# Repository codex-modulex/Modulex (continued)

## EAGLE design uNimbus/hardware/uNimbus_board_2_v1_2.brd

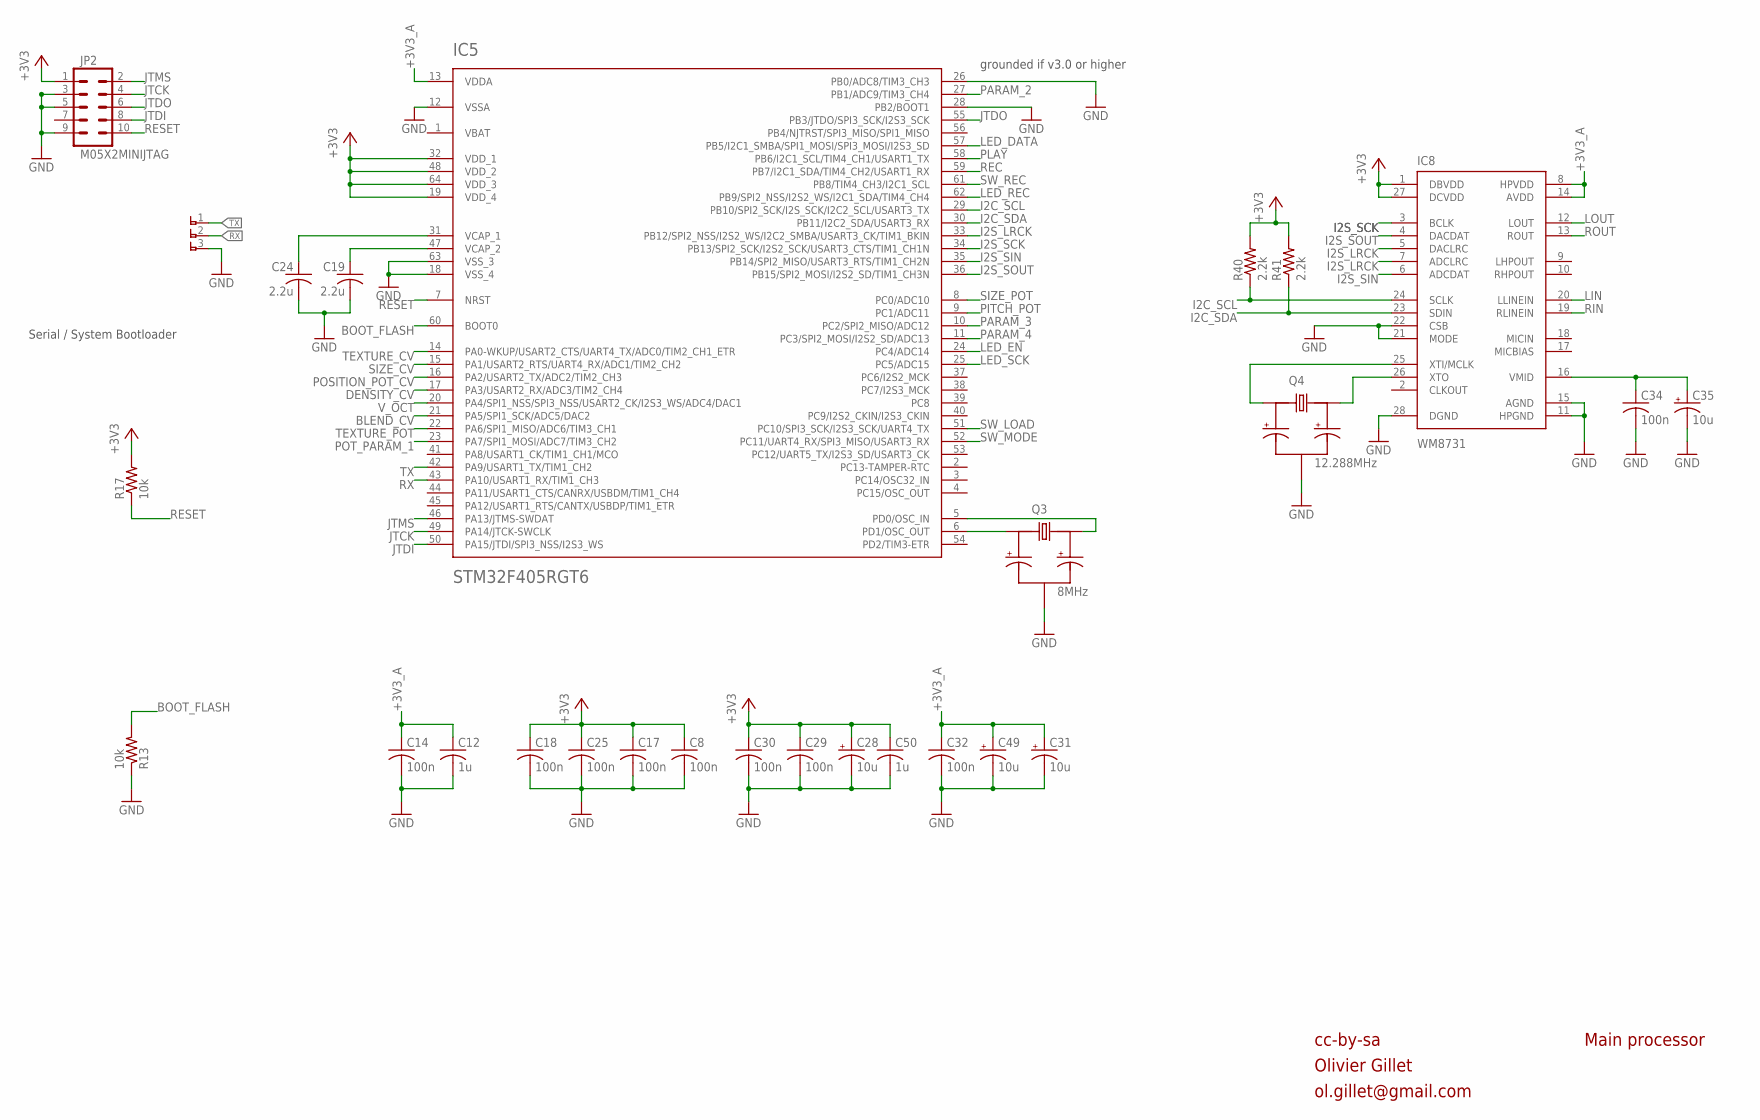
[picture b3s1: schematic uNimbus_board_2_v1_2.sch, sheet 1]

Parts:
C8, C32, C34: 100n; C0603
C12, C50: 1u; C0603K
C14, C17, C18, C25, C29, C30: 100n; C0603K
C19, C24: 2.2u; C0805K
C28: 10u; 153CLV-0405
C31, C35: 10u; PANASONIC_B
C49: 10u; PANASONIC_A
IC5: STM32F405RGT6; TQFP-10X10-64
IC8: WM8731; SSOP28
JP2: M05X2MINIJTAG; 2X5-1.27
Q3: 8MHz; CRYSTAL_SMALLER
Q4: 12.288MHz; CRYSTAL_SMALLER
R13, R17: 10k; PARTS_AMAN_RESISTOR_0603
R40, R41: 2.2k; PARTS_AMAN_RESISTOR_0603
U$4: 1X3_SMALL

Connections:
+3V3: C8.1, C17.1, C18.1, C25.1, C28.+, C29.1, C30.1, C50.1, IC5.19 (VDD_4), IC5.32 (VDD_1), IC5.48 (VDD_2), IC5.64 (VDD_3), IC8.1 (DBVDD), IC8.27 (DCVDD), JP2.1, R17.2, R40.2, R41.2; also elsewhere on the board
+3V3_A: C12.1, C14.1, C31.+, C32.1, C49.+, IC5.13 (VDDA), IC8.8 (HPVDD), IC8.14 (AVDD); also elsewhere on the board
BLEND_CV: IC5.21 (PA5/SPI1_SCK/ADC5/DAC2); also elsewhere on the board
BOOT_FLASH: IC5.60 (BOOT0), R13.2
DENSITY_CV: IC5.17 (PA3/USART2_RX/ADC3/TIM2_CH4); also elsewhere on the board
GND: C8.2, C12.2, C14.2, C17.2, C18.2, C19.2, C24.2, C25.2, C28.-, C29.2, C30.2, C31.-, C32.2, C34.2, C35.-, C49.-, C50.2, IC5.12 (VSSA), IC5.18 (VSS_4), IC5.26 (PB0/ADC8/TIM3_CH3), IC5.28 (PB2/BOOT1), IC5.63 (VSS_3), IC8.11 (HPGND), IC8.15 (AGND), IC8.21 (MODE), IC8.22 (CSB), IC8.28 (DGND), JP2.3, JP2.5, JP2.9, Q3.GND, Q4.GND, R13.1, U$4.3; also elsewhere on the board
I2C_SCL: IC5.29 (PB10/SPI2_SCK/I2S_SCK/I2C2_SCL/USART3_TX), IC8.24 (SCLK), R40.1
I2C_SDA: IC5.30 (PB11/I2C2_SDA/USART3_RX), IC8.23 (SDIN), R41.1
I2S_LRCK: IC5.33 (PB12/SPI2_NSS/I2S2_WS/I2C2_SMBA/USART3_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), IC8.5 (DACLRC), IC8.7 (ADCLRC)
I2S_SCK: IC5.34 (PB13/SPI2_SCK/I2S2_SCK/USART3_CTS/TIM1_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), IC8.3 (BCLK)
I2S_SIN: IC5.35 (PB14/SPI2_MISO/USART3_RTS/TIM1_CH2N), IC8.6 (ADCDAT)
I2S_SOUT: IC5.36 (PB15/SPI2_MOSI/I2S2_SD/TIM1_CH3N), IC8.4 (DACDAT)
JTCK: IC5.49 (PA14/JTCK-SWCLK), JP2.4
JTDI: IC5.50 (PA15/JTDI/SPI3_NSS/I2S3_WS), JP2.8
JTDO: IC5.55 (PB3/JTDO/SPI3_SCK/I2S3_SCK), JP2.6
JTMS: IC5.46 (PA13/JTMS-SWDAT), JP2.2
LED_DATA: IC5.57 (PB5/I2C1_SMBA/SPI1_MOSI/SPI3_MOSI/I2S3_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); also elsewhere on the board
LED_EN: IC5.24 (PC4/ADC14); also elsewhere on the board
LED_REC: IC5.62 (PB9/SPI2_NSS/I2S2_WS/I2C1_SDA/TIM4_CH4); also elsewhere on the board
LED_SCK: IC5.25 (PC5/ADC15); also elsewhere on the board
LIN: IC8.20 (LLINEIN); also elsewhere on the board
LOUT: IC8.12 (LOUT); also elsewhere on the board
unnamed: IC5.6 (PD1/OSC_OUT), Q3.X1
unnamed: IC8.25 (XTI/MCLK), Q4.X1
unnamed: IC5.5 (PD0/OSC_IN), Q3.X2
unnamed: C19.1, IC5.47 (VCAP_2)
unnamed: C34.1, C35.+, IC8.16 (VMID)
unnamed: C24.1, IC5.31 (VCAP_1)
unnamed: IC8.26 (XTO), Q4.X2
PARAM_2: IC5.27 (PB1/ADC9/TIM3_CH4); also elsewhere on the board
PARAM_3: IC5.10 (PC2/SPI2_MISO/ADC12); also elsewhere on the board
PARAM_4: IC5.11 (PC3/SPI2_MOSI/I2S2_SD/ADC13); also elsewhere on the board
PITCH_POT: IC5.9 (PC1/ADC11); also elsewhere on the board
PLAY: IC5.58 (PB6/I2C1_SCL/TIM4_CH1/USART1_TX); also elsewhere on the board
POSITION_POT_CV: IC5.16 (PA2/USART2_TX/ADC2/TIM2_CH3); also elsewhere on the board
POT_PARAM_1: IC5.23 (PA7/SPI1_MOSI/ADC7/TIM3_CH2); also elsewhere on the board
REC: IC5.59 (PB7/I2C1_SDA/TIM4_CH2/USART1_RX); also elsewhere on the board
RESET: IC5.7 (NRST), JP2.10, R17.1
RIN: IC8.19 (RLINEIN); also elsewhere on the board
ROUT: IC8.13 (ROUT); also elsewhere on the board
RX: IC5.43 (PA10/USART1_RX/TIM1_CH3), U$4.2
SIZE_CV: IC5.15 (PA1/USART2_RTS/UART4_RX/ADC1/TIM2_CH2); also elsewhere on the board
SIZE_POT: IC5.8 (PC0/ADC10); also elsewhere on the board
SW_LOAD: IC5.51 (PC10/SPI3_SCK/I2S3_SCK/UART4_TX); also elsewhere on the board
SW_MODE: IC5.52 (PC11/UART4_RX/SPI3_MISO/USART3_RX); also elsewhere on the board
SW_REC: IC5.61 (PB8/TIM4_CH3/I2C1_SCL); also elsewhere on the board
TEXTURE_CV: IC5.14 (PA0-WKUP/USART2_CTS/UART4_TX/ADC0/TIM2_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); also elsewhere on the board
TEXTURE_POT: IC5.22 (PA6/SPI1_MISO/ADC6/TIM3_CH1); also elsewhere on the board
TX: IC5.42 (PA9/USART1_TX/TIM1_CH2), U$4.1
VBAT: IC5.1 (VBAT)
V_OCT: IC5.20 (PA4/SPI1_NSS/SPI3_NSS/USART2_CK/I2S3_WS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); also elsewhere on the board

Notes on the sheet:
cc-by-sa
Olivier Gillet
ol.gillet@gmail.com
Main processor
Serial / System Bootloader
grounded if v3.0 or higher

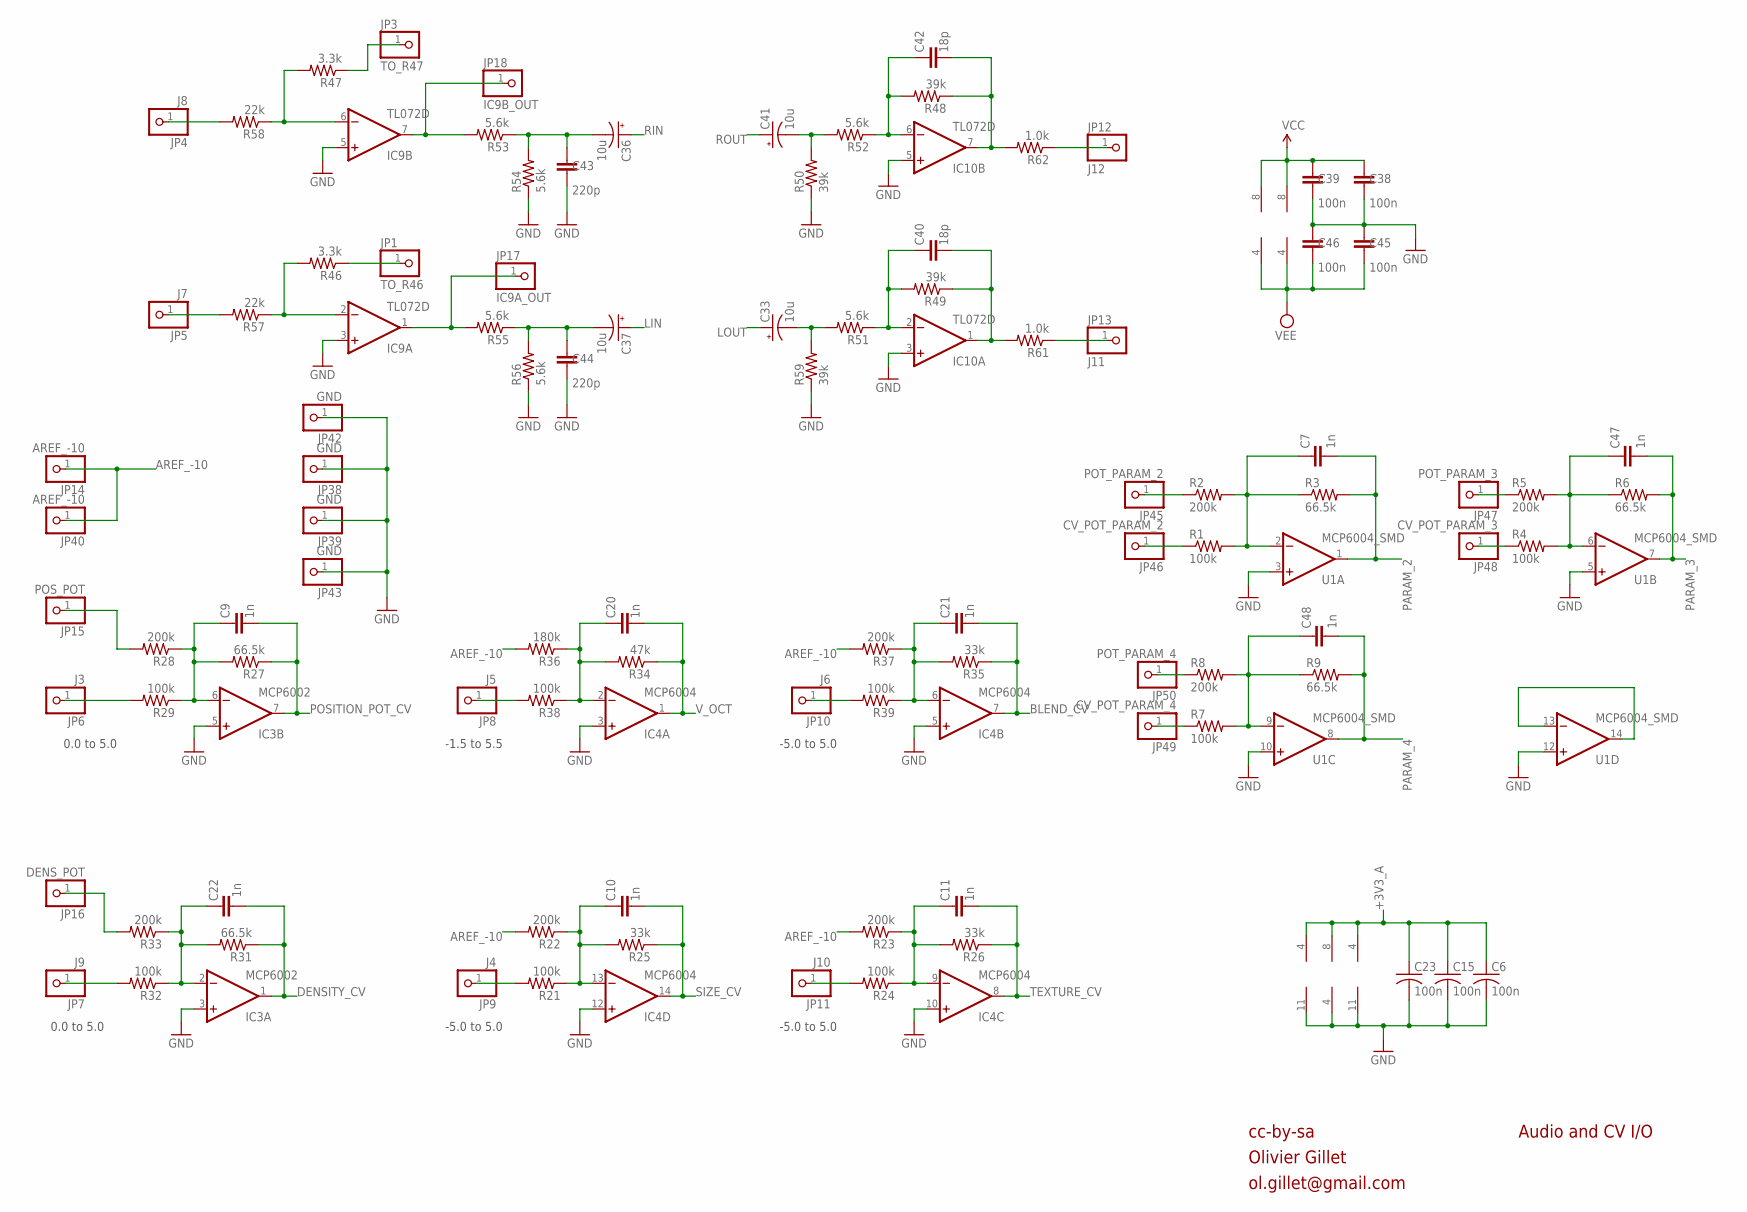
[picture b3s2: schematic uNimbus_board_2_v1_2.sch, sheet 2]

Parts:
C6, C15: 100n; C0603K
C7, C9, C10, C11, C20, C21, C22, C47, C48: 1n; PARTS_AMAN_RESISTOR_0603
C23: 100n; C0603
C33, C36, C37, C41: 10u; PANASONIC_B
C38, C39, C45, C46: 100n; PARTS_AMAN_RESISTOR_0603
C40, C42: 18p; PARTS_AMAN_RESISTOR_0603
C43, C44: 220p; PARTS_AMAN_RESISTOR_0603
IC3: MCP6002; SO08
IC4: MCP6004; SO14
IC9, IC10: TL072D; SO08
JP1: TO_R46; PARTS_AMAN_1X01
JP3: TO_R47; PARTS_AMAN_1X01
JP4: J8; PARTS_AMAN_1X01
JP5: J7; PARTS_AMAN_1X01
JP6: J3; PARTS_AMAN_1X01
JP7: J9; PARTS_AMAN_1X01
JP8: J5; PARTS_AMAN_1X01
JP9: J4; PARTS_AMAN_1X01
JP10: J6; PARTS_AMAN_1X01
JP11: J10; PARTS_AMAN_1X01
JP12: J12; PARTS_AMAN_1X01
JP13: J11; PARTS_AMAN_1X01
JP14, JP40: AREF_-10; PARTS_AMAN_1X01
JP15: POS_POT; PARTS_AMAN_1X01
JP16: DENS_POT; PARTS_AMAN_1X01
JP17: IC9A_OUT; PARTS_AMAN_1X01
JP18: IC9B_OUT; PARTS_AMAN_1X01
JP38, JP39, JP42, JP43: GND; PARTS_AMAN_1X01
JP45: POT_PARAM_2; PARTS_AMAN_1X01
JP46: CV_POT_PARAM_2; PARTS_AMAN_1X01
JP47: POT_PARAM_3; PARTS_AMAN_1X01
JP48: CV_POT_PARAM_3; PARTS_AMAN_1X01
JP49: CV_POT_PARAM_4; PARTS_AMAN_1X01
JP50: POT_PARAM_4; PARTS_AMAN_1X01
R1, R4, R7, R21, R24, R29, R32, R38, R39: 100k; PARTS_AMAN_RESISTOR_0603
R2, R5, R8, R22, R23, R28, R33, R37: 200k; PARTS_AMAN_RESISTOR_0603
R3, R6, R9, R27, R31: 66.5k; PARTS_AMAN_RESISTOR_0603
R25, R26, R35: 33k; PARTS_AMAN_RESISTOR_0603
R34: 47k; PARTS_AMAN_RESISTOR_0603
R36: 180k; PARTS_AMAN_RESISTOR_0603
R46, R47: 3.3k; PARTS_AMAN_RESISTOR_0603
R48, R49, R50, R59: 39k; PARTS_AMAN_RESISTOR_0603
R51, R52, R53, R54, R55, R56: 5.6k; PARTS_AMAN_RESISTOR_0603
R57, R58: 22k; PARTS_AMAN_RESISTOR_0603
R61, R62: 1.0k; PARTS_AMAN_RESISTOR_0603
U1: MCP6004_SMD; SO14

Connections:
+3V3_A: C6.1, C15.1, C23.1, IC3.8 (V+), IC4.4 (V+), U1.4 (V+); also elsewhere on the board
AREF_-10: JP14.1, JP40.1, R22.2, R23.2, R36.2, R37.2; also elsewhere on the board
BLEND_CV: C21.2, IC4.7 (OUT), R35.1; also elsewhere on the board
DENSITY_CV: C22.2, IC3.1 (OUT), R31.1; also elsewhere on the board
GND: C6.2, C15.2, C23.2, C38.2, C39.2, C43.2, C44.2, C45.1, C46.1, IC3.3 (+IN), IC3.4 (V-), IC3.5 (+IN), IC4.3 (+IN), IC4.5 (+IN), IC4.10 (+IN), IC4.11 (V-), IC4.12 (+IN), IC9.3 (+IN), IC9.5 (+IN), IC10.3 (+IN), IC10.5 (+IN), JP38.1, JP39.1, JP42.1, JP43.1, R50.1, R54.1, R56.1, R59.1, U1.3 (+IN), U1.5 (+IN), U1.10 (+IN), U1.11 (V-), U1.12 (+IN); also elsewhere on the board
LIN: C37.+; also elsewhere on the board
LOUT: C33.+; also elsewhere on the board
LOUT_JACK: JP13.1, R61.1
unnamed: JP9.1, R21.2
unnamed: C10.1, IC4.13 (-IN), R21.1, R22.1, R25.2
unnamed: JP11.1, R24.2
unnamed: C11.1, IC4.9 (-IN), R23.1, R24.1, R26.2
unnamed: JP10.1, R39.2
unnamed: JP46.1, R1.1
unnamed: JP8.1, R38.2
unnamed: C20.1, IC4.2 (-IN), R34.2, R36.1, R38.1
unnamed: C7.1, R1.2, R2.2, R3.1, U1.2 (-IN)
unnamed: JP7.1, R32.2
unnamed: C21.1, IC4.6 (-IN), R35.2, R37.1, R39.1
unnamed: JP45.1, R2.1
unnamed: C37.-, C44.1, R55.1, R56.2
unnamed: JP4.1, R58.2
unnamed: JP5.1, R57.2
unnamed: C36.-, C43.1, R53.1, R54.2
unnamed: C41.-, R50.2, R52.2
unnamed: C22.1, IC3.2 (-IN), R31.2, R32.1, R33.1
unnamed: C42.1, IC10.6 (-IN), R48.2, R52.1
unnamed: JP16.1, R33.2
unnamed: JP6.1, R29.2
unnamed: C42.2, IC10.7 (OUT), R48.1, R62.2
unnamed: JP47.1, R5.1
unnamed: C9.1, IC3.6 (-IN), R27.2, R28.1, R29.1
unnamed: C33.-, R51.2, R59.2
unnamed: C40.1, IC10.2 (-IN), R49.2, R51.1
unnamed: C40.2, IC10.1 (OUT), R49.1, R61.2
unnamed: U1.13 (-IN), U1.14 (OUT)
unnamed: JP15.1, R28.2
unnamed: JP48.1, R4.1
unnamed: C47.1, R4.2, R5.2, R6.1, U1.6 (-IN)
unnamed: JP1.1, R46.1
unnamed: JP49.1, R7.1
unnamed: JP50.1, R8.1
unnamed: IC9.7 (OUT), JP18.1, R53.2
unnamed: JP3.1, R47.1
unnamed: IC9.6 (-IN), R47.2, R58.1
unnamed: IC9.1 (OUT), JP17.1, R55.2
unnamed: IC9.2 (-IN), R46.2, R57.1
unnamed: C48.1, R7.2, R8.2, R9.1, U1.9 (-IN)
PARAM_2: C7.2, R3.2, U1.1 (OUT); also elsewhere on the board
PARAM_3: C47.2, R6.2, U1.7 (OUT); also elsewhere on the board
PARAM_4: C48.2, R9.2, U1.8 (OUT); also elsewhere on the board
POSITION_POT_CV: C9.2, IC3.7 (OUT), R27.1; also elsewhere on the board
RIN: C36.+; also elsewhere on the board
ROUT: C41.+; also elsewhere on the board
ROUT_JACK: JP12.1, R62.1
SIZE_CV: C10.2, IC4.14 (OUT), R25.1; also elsewhere on the board
TEXTURE_CV: C11.2, IC4.8 (OUT), R26.1; also elsewhere on the board
VCC: C38.1, C39.1, IC9.8 (V+), IC10.8 (V+); also elsewhere on the board
VEE: C45.2, C46.2, IC9.4 (V-), IC10.4 (V-); also elsewhere on the board
V_OCT: C20.2, IC4.1 (OUT), R34.1; also elsewhere on the board

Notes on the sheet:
cc-by-sa
Olivier Gillet
ol.gillet@gmail.com
Audio and CV I/O
0.0 to 5.0
-1.5 to 5.5
-5.0 to 5.0

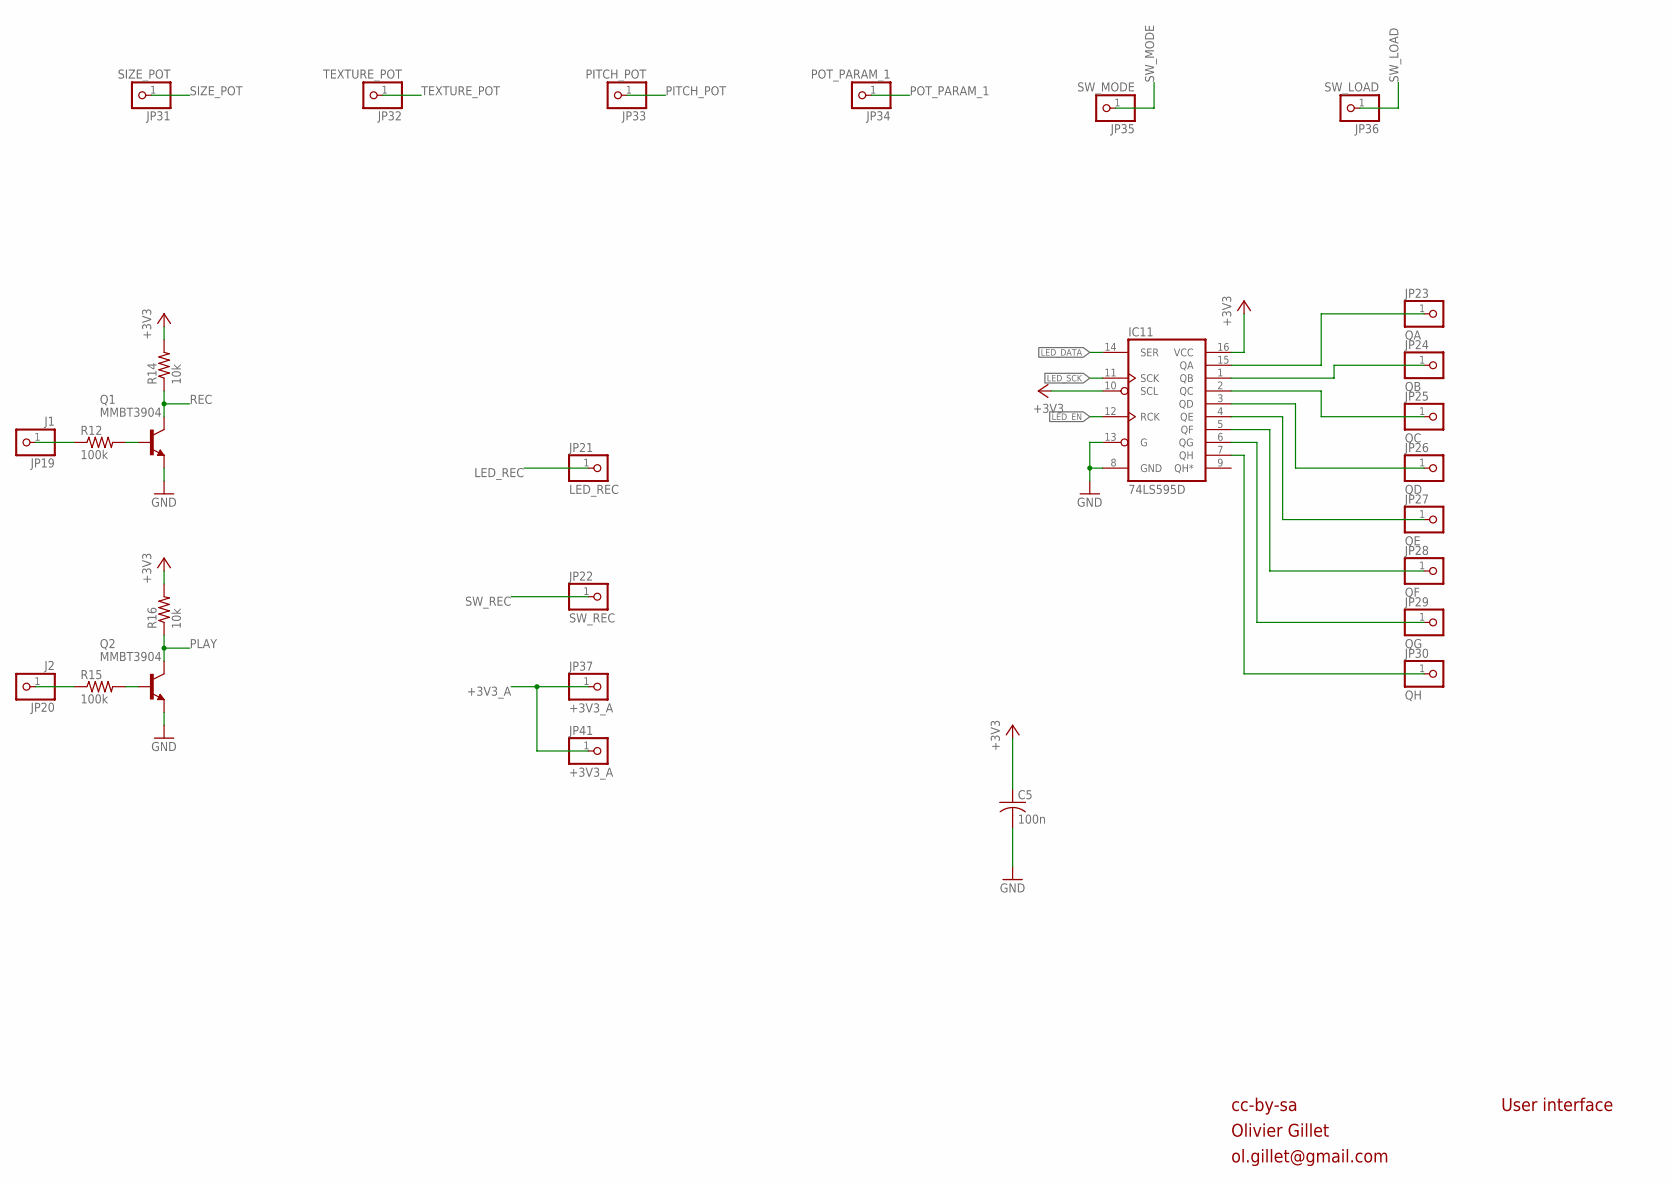
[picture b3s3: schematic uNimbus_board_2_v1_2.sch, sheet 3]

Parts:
C5: 100n; C0603
IC11: 74LS595D; SO16
JP19: J1; PARTS_AMAN_1X01
JP20: J2; PARTS_AMAN_1X01
JP21: LED_REC; PARTS_AMAN_1X01
JP22: SW_REC; PARTS_AMAN_1X01
JP23: QA; PARTS_AMAN_1X01
JP24: QB; PARTS_AMAN_1X01
JP25: QC; PARTS_AMAN_1X01
JP26: QD; PARTS_AMAN_1X01
JP27: QE; PARTS_AMAN_1X01
JP28: QF; PARTS_AMAN_1X01
JP29: QG; PARTS_AMAN_1X01
JP30: QH; PARTS_AMAN_1X01
JP31: SIZE_POT; PARTS_AMAN_1X01
JP32: TEXTURE_POT; PARTS_AMAN_1X01
JP33: PITCH_POT; PARTS_AMAN_1X01
JP34: POT_PARAM_1; PARTS_AMAN_1X01
JP35: SW_MODE; PARTS_AMAN_1X01
JP36: SW_LOAD; PARTS_AMAN_1X01
JP37, JP41: +3V3_A; PARTS_AMAN_1X01
Q1, Q2: MMBT3904; SOT23-BEC
R12, R15: 100k; R0603
R14, R16: 10k; R0603

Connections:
+3V3: C5.1, IC11.10 (SCL), IC11.16 (VCC), R14.2, R16.2; also elsewhere on the board
+3V3_A: JP37.1, JP41.1; also elsewhere on the board
GND: C5.2, IC11.8 (GND), IC11.13 (G), Q1.E, Q2.E; also elsewhere on the board
LED_DATA: IC11.14 (SER); also elsewhere on the board
LED_EN: IC11.12 (RCK); also elsewhere on the board
LED_REC: JP21.1; also elsewhere on the board
LED_SCK: IC11.11 (SCK); also elsewhere on the board
unnamed: JP20.1, R15.1
unnamed: Q2.B, R15.2
unnamed: IC11.15 (QA), JP23.1
unnamed: IC11.1 (QB), JP24.1
unnamed: IC11.2 (QC), JP25.1
unnamed: IC11.3 (QD), JP26.1
unnamed: IC11.4 (QE), JP27.1
unnamed: IC11.5 (QF), JP28.1
unnamed: JP19.1, R12.1
unnamed: IC11.6 (QG), JP29.1
unnamed: IC11.7 (QH), JP30.1
unnamed: Q1.B, R12.2
PITCH_POT: JP33.1; also elsewhere on the board
PLAY: Q2.C, R16.1; also elsewhere on the board
POT_PARAM_1: JP34.1; also elsewhere on the board
REC: Q1.C, R14.1; also elsewhere on the board
SIZE_POT: JP31.1; also elsewhere on the board
SW_LOAD: JP36.1; also elsewhere on the board
SW_MODE: JP35.1; also elsewhere on the board
SW_REC: JP22.1; also elsewhere on the board
TEXTURE_POT: JP32.1; also elsewhere on the board

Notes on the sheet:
cc-by-sa
Olivier Gillet
ol.gillet@gmail.com
User interface

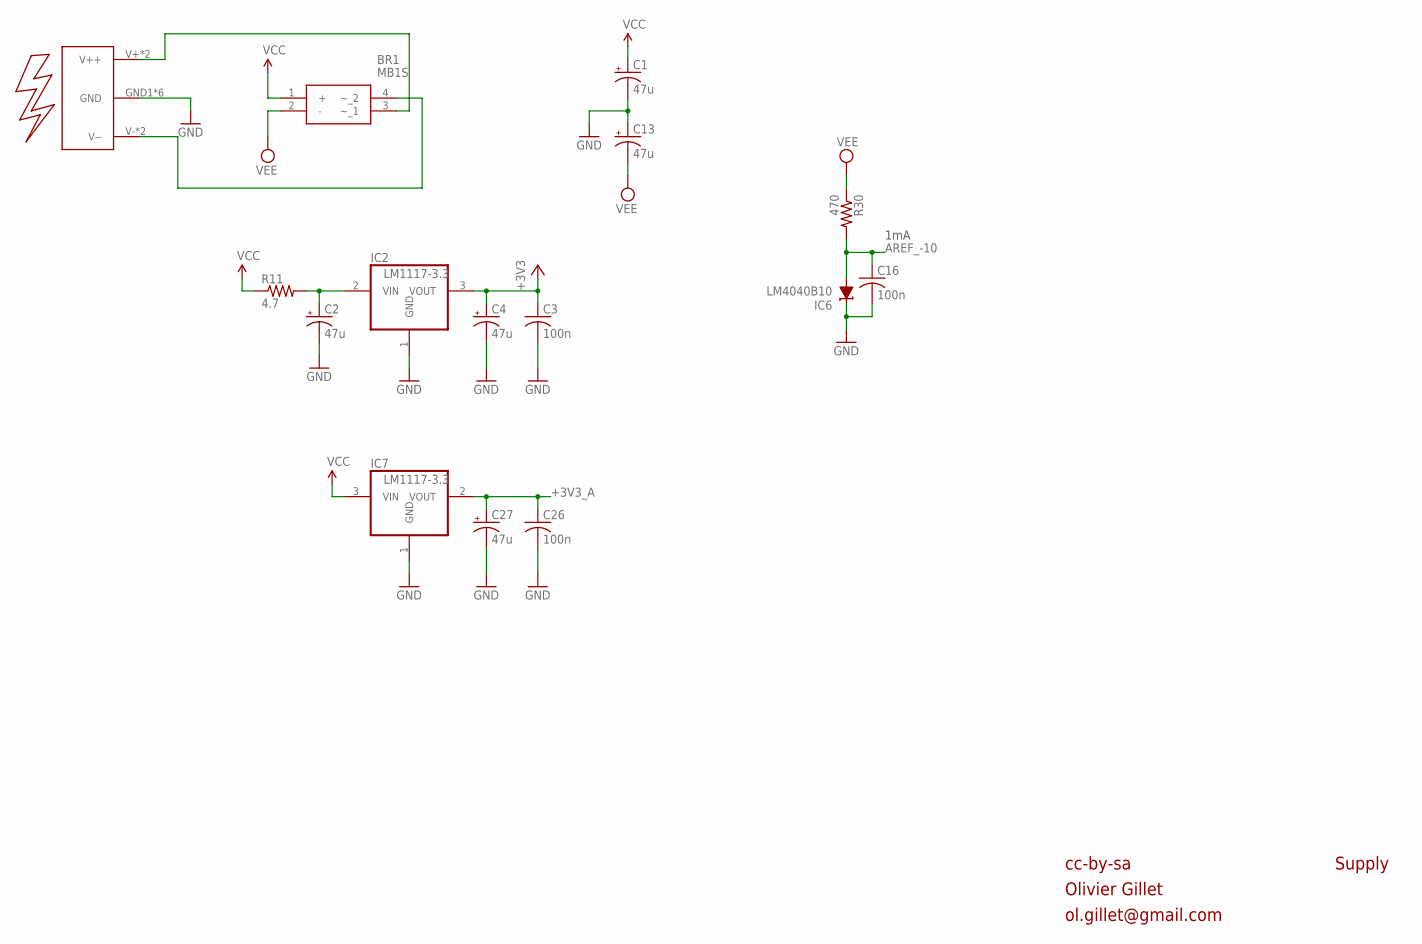
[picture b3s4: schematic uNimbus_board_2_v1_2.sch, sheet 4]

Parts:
BR1: MB1S; SOP245P670X290-4N
C1, C2, C4, C13, C27: 47u; 153CLV-0505
C3, C16, C26: 100n; C0603
IC2: LM1117-3.3; TO252
IC6: LM4040B10; DBZ_R-PDSO-G3
IC7: LM1117-3.3; SOT223
R11: 4.7; R1206
R30: 470; R0603
U$2: EURO_POWER2

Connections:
+3V3: C3.1, C4.+, IC2.3 (VOUT); also elsewhere on the board
+3V3_A: C26.1, C27.+, IC7.2 (VOUT); also elsewhere on the board
AREF_-10: C16.1, IC6.2 (A), R30.2; also elsewhere on the board
GND: C1.-, C2.-, C3.2, C4.-, C13.+, C16.2, C26.2, C27.-, IC2.1 (GND), IC6.1 (C), IC7.1 (GND), U$2.GND1 (GND), U$2.GND2 (GND), U$2.GND3 (GND), U$2.GND4 (GND), U$2.GND5 (GND), U$2.GND6 (GND); also elsewhere on the board
unnamed: C2.+, IC2.2 (VIN), R11.2
unnamed: BR1.3 (~_1), U$2.V+ (V++), U$2.V++
unnamed: BR1.4 (~_2), U$2.V- (V--), U$2.V--
VCC: BR1.1 (+), C1.+, IC7.3 (VIN), R11.1; also elsewhere on the board
VEE: BR1.2 (-), C13.-, R30.1; also elsewhere on the board

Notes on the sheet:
1mA
cc-by-sa
Olivier Gillet
ol.gillet@gmail.com
Supply

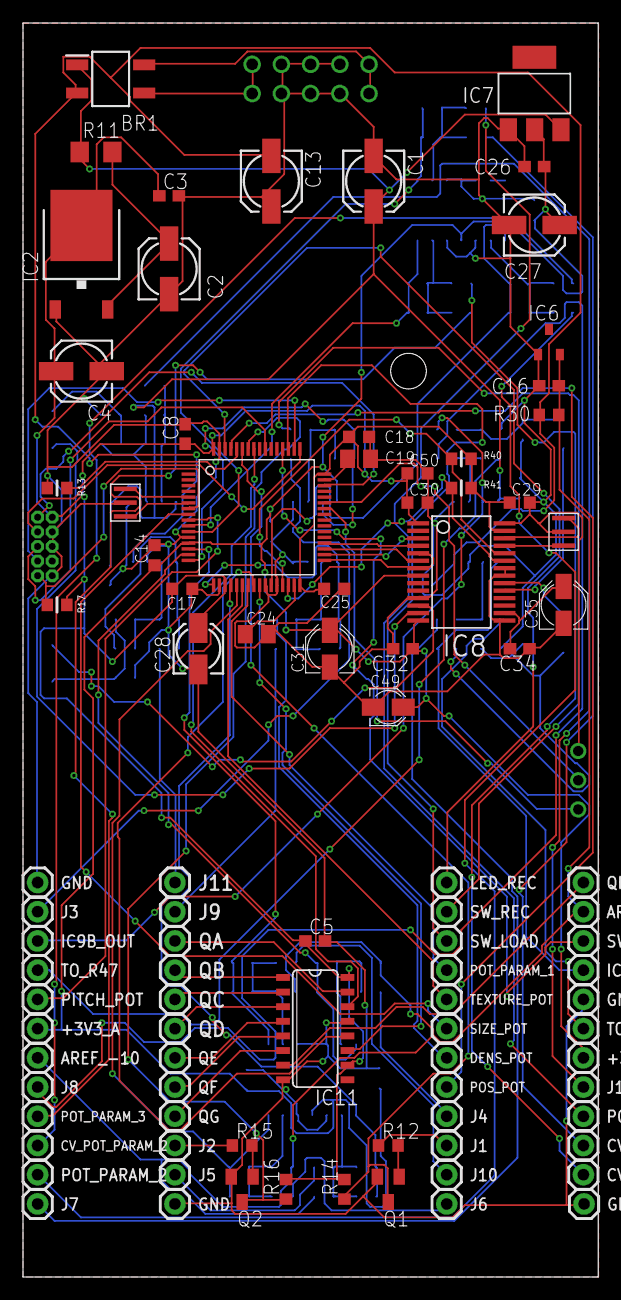
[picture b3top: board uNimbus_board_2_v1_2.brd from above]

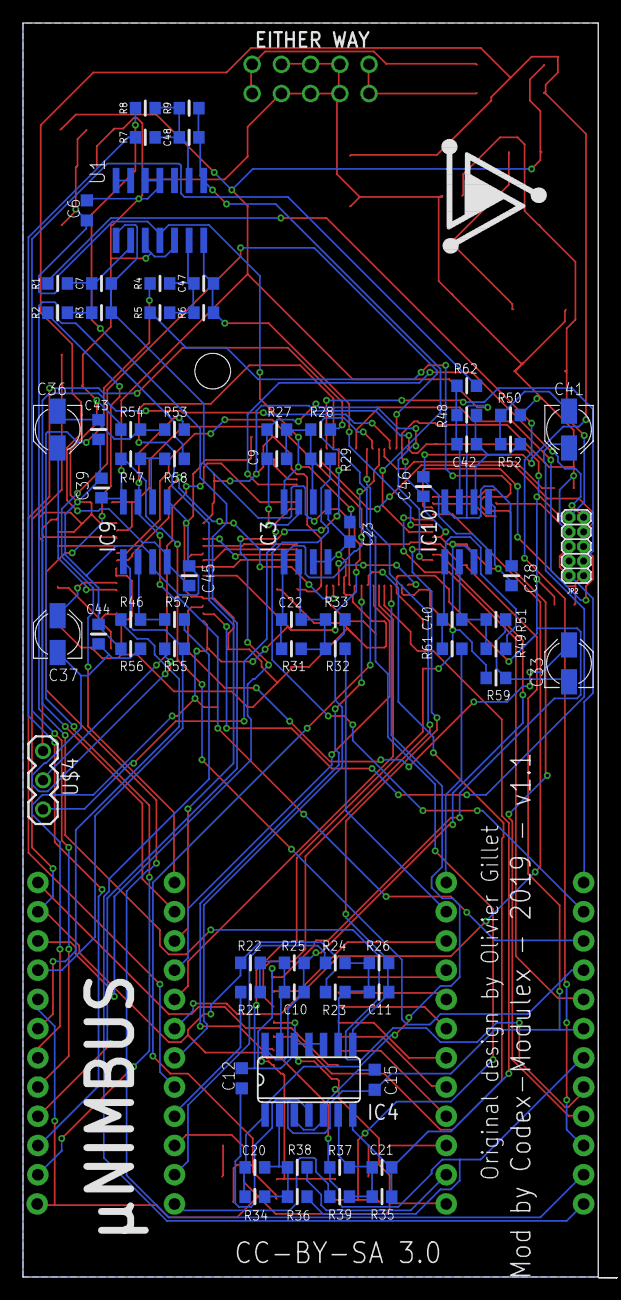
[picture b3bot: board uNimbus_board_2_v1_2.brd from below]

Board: 2 copper layers, 50.0 x 109.0 mm, 170 parts (75 on the bottom side), 110 nets.

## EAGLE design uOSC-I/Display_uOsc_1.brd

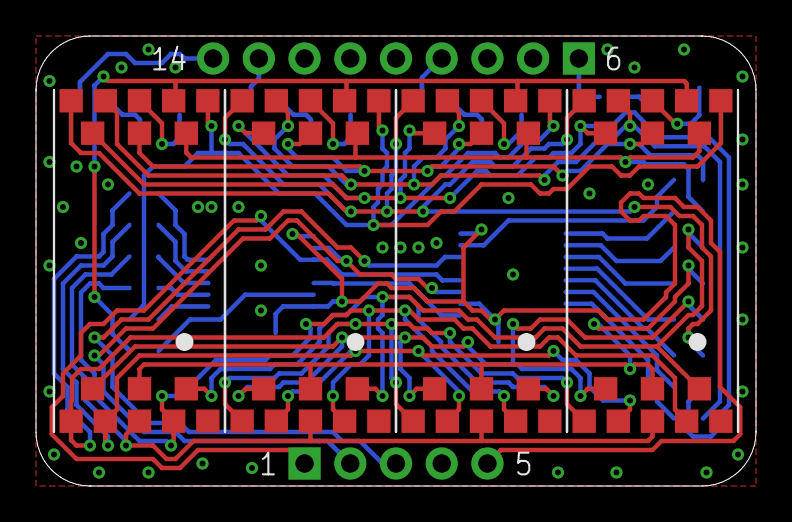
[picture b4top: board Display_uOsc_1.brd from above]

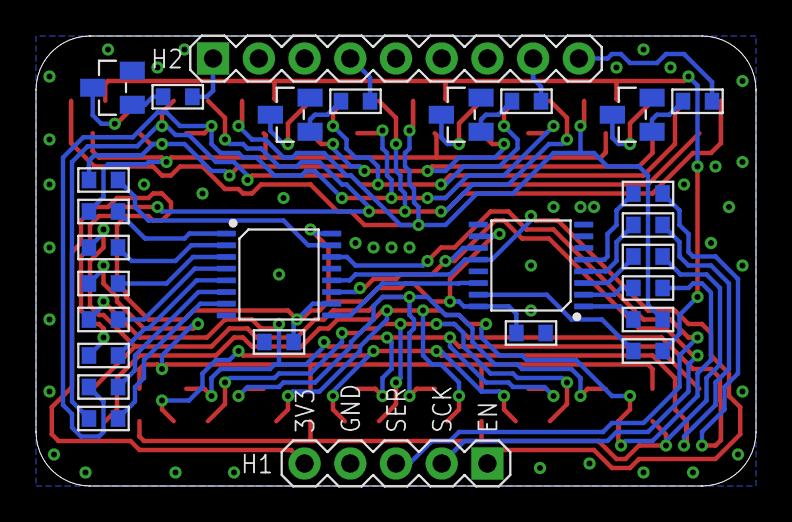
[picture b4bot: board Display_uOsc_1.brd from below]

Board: 2 copper layers, 40.0 x 25.0 mm, 32 parts (28 on the bottom side), 46 nets.

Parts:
A1, A2, A3, A4: 14-SEGMENT-SMD; 14-SEGMENT-0.4"-SMD
C1, C2: 0.1uF; 0603-NP
H1: HEADER-1X05-PTH-2.54-MALE
H2: HEADER-1X09-PTH-2.54-MALE
Q1, Q2, Q3, Q4: NPN-SOT23-BEC; SOT-23
R1, R2, R3, R4: 1k; 0603-NP
R5, R6, R7, R8, R9, R10, R11, R12, R13, R14, R15, R16, R17, R18: 100R; 0603-NP
U1, U2: SN74HC595-TSSOP-16; TSSOP-16

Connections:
3V3: C1.1, C2.1, H1.5, U1.10, U1.16, U2.10, U2.16
A: A1.10, A2.10, A3.10, A4.10, R5.2
A1C: A1.14, Q1.3
A2C: A2.14, Q2.3
A3C: A3.14, Q3.3
A4C: A4.14, Q4.3
B: A1.11, A2.11, A3.11, A4.11, R6.2
C: A1.6, A2.6, A3.6, A4.6, R7.2
D: A1.7, A2.7, A3.7, A4.7, R8.2
DISP_CHAR1: H2.9, R1.1
DISP_CHAR2: H2.8, R2.1
DISP_CHAR3: H2.4, R3.1
DISP_CHAR4: H2.1, R4.1
DISP_EN: H1.1, U1.12, U2.12
DISP_SCK: H1.2, U1.11, U2.11
DISP_SER: H1.3, U1.14
E: A1.8, A2.8, A3.8, A4.8, R9.2
F: A1.16, A2.16, A3.16, A4.16, R10.2
G: A1.9, A2.9, A3.9, A4.9, R11.2
GND: C1.2, C2.2, H1.4, H2.2, H2.3, H2.5, H2.6, H2.7, Q1.2, Q2.2, Q3.2, Q4.2, U1.8, U1.13, U2.8, U2.13
H: A1.15, A2.15, A3.15, A4.15, R12.2
J: A1.13, A2.13, A3.13, A4.13, R13.2
K: A1.12, A2.12, A3.12, A4.12, R14.2
L: A1.4, A2.4, A3.4, A4.4, R15.2
M: A1.3, A2.3, A3.3, A4.3, R16.2
N: A1.2, A2.2, A3.2, A4.2, R17.2
P: A1.1, A2.1, A3.1, A4.1, R18.2
Q1B: Q1.1, R1.2
Q2B: Q2.1, R2.2
Q3B: Q3.1, R3.2
Q4B: Q4.1, R4.2
RA: R5.1, U1.15
RB: R6.1, U1.1
RC: R7.1, U1.2
RD: R8.1, U1.3
RE: R9.1, U1.4
RF: R10.1, U1.5
RG: R11.1, U1.6
RH: R12.1, U1.7
RJ: R13.1, U2.15
RK: R14.1, U2.1
RL: R15.1, U2.2
RM: R16.1, U2.3
RN: R17.1, U2.4
RP: R18.1, U2.5
U1-U2: U1.9, U2.14

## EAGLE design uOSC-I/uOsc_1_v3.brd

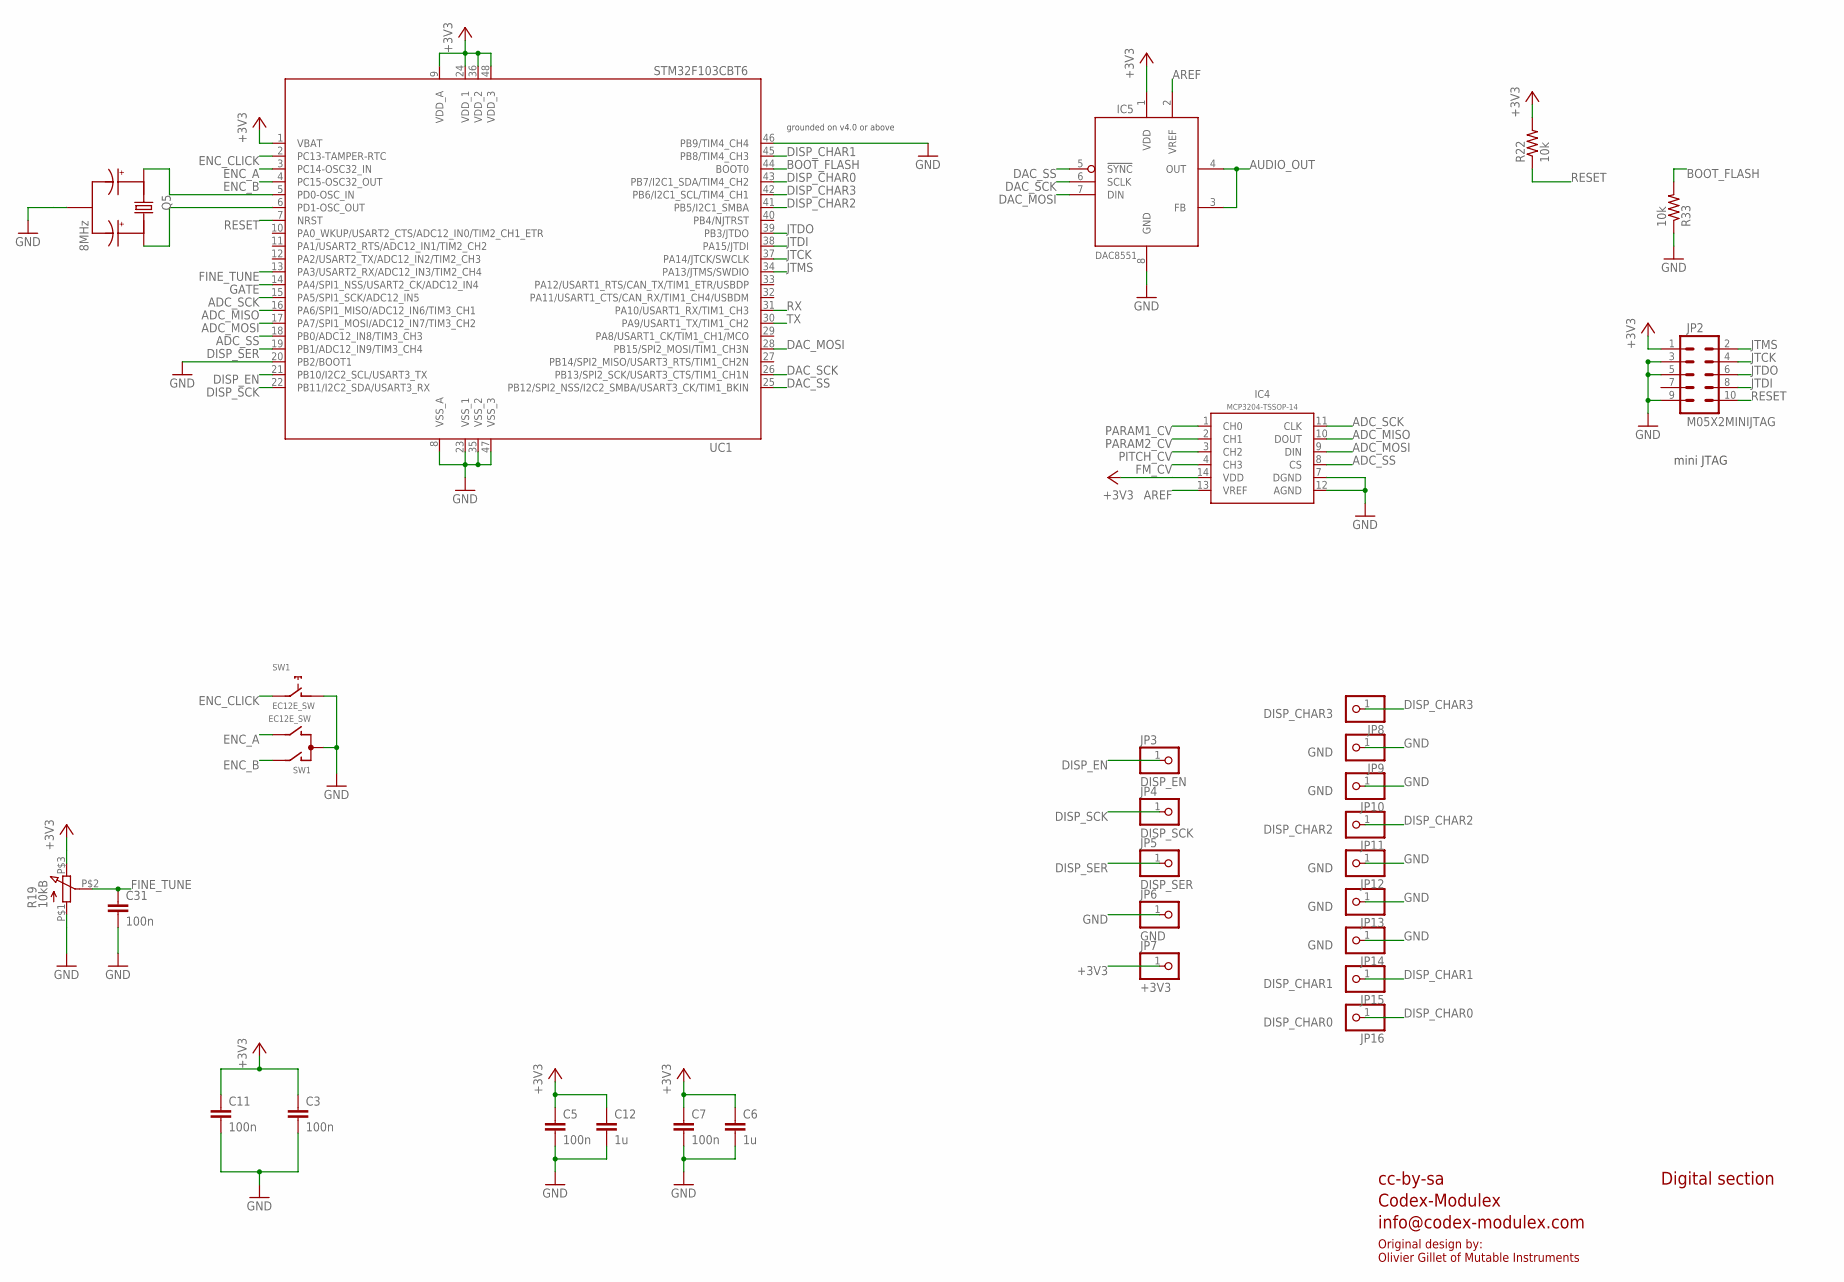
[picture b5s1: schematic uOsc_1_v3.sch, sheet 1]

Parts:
C3, C5, C7, C11, C31: 100n; PARTS_AMAN_RESISTOR_0603
C6, C12: 1u; PARTS_AMAN_RESISTOR_0603
IC4: MCP3204-TSSOP-14; UBRAIDS_SE_TSSOP-14
IC5: DAC8551; MSOP-8
JP2: M05X2MINIJTAG; 2X5-1.27
JP3: DISP_EN; PARTS_AMAN_1X01
JP4: DISP_SCK; PARTS_AMAN_1X01
JP5: DISP_SER; PARTS_AMAN_1X01
JP6, JP9, JP10, JP12, JP13, JP14: GND; PARTS_AMAN_1X01
JP7: +3V3; PARTS_AMAN_1X01
JP8: DISP_CHAR3; PARTS_AMAN_1X01
JP11: DISP_CHAR2; PARTS_AMAN_1X01
JP15: DISP_CHAR1; PARTS_AMAN_1X01
JP16: DISP_CHAR0; PARTS_AMAN_1X01
Q5: 8MHz; CRYSTAL_SMALLER
R19: 10kB; Q-POT2
R22, R33: 10k; PARTS_AMAN_RESISTOR_0603
SW1: EC12E_SW; ALPS_EC12E_SW
UC1: STM32F103CBT6; LQFP48

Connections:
+3V3: C3.1, C5.1, C6.1, C7.1, C11.1, C12.1, IC4.14 (VDD), IC5.1 (VDD), JP2.1, JP7.1, R19.P$3 (3), R22.2, UC1.1 (VBAT), UC1.9 (VDD_A), UC1.24 (VDD_1), UC1.36 (VDD_2), UC1.48 (VDD_3); also elsewhere on the board
ADC_MISO: IC4.10 (DOUT), UC1.16 (PA6/SPI1_MISO/ADC12_IN6/TIM3_CH1)
ADC_MOSI: IC4.9 (DIN), UC1.17 (PA7/SPI1_MOSI/ADC12_IN7/TIM3_CH2)
ADC_SCK: IC4.11 (CLK), UC1.15 (PA5/SPI1_SCK/ADC12_IN5)
ADC_SS: IC4.8 (CS), UC1.18 (PB0/ADC12_IN8/TIM3_CH3)
AREF: IC4.13 (VREF), IC5.2 (VREF); also elsewhere on the board
AUDIO_OUT: IC5.3 (FB), IC5.4 (OUT); also elsewhere on the board
BOOT_FLASH: R33.2, UC1.44 (BOOT0)
DAC_MOSI: IC5.7 (DIN), UC1.28 (PB15/SPI2_MOSI/TIM1_CH3N)
DAC_SCK: IC5.6 (SCLK), UC1.26 (PB13/SPI2_SCK/USART3_CTS/TIM1_CH1N)
DAC_SS: IC5.5 (!SYNC), UC1.25 (PB12/SPI2_NSS/I2C2_SMBA/USART3_CK/TIM1_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)
DISP_CHAR0: JP16.1, UC1.43 (PB7/I2C1_SDA/TIM4_CH2)
DISP_CHAR1: JP15.1, UC1.45 (PB8/TIM4_CH3)
DISP_CHAR2: JP11.1, UC1.41 (PB5/I2C1_SMBA)
DISP_CHAR3: JP8.1, UC1.42 (PB6/I2C1_SCL/TIM4_CH1)
DISP_EN: JP3.1, UC1.21 (PB10/I2C2_SCL/USART3_TX)
DISP_SCK: JP4.1, UC1.22 (PB11/I2C2_SDA/USART3_RX)
DISP_SER: JP5.1, UC1.19 (PB1/ADC12_IN9/TIM3_CH4)
ENC_A: SW1.B, UC1.3 (PC14-OSC32_IN)
ENC_B: SW1.A, UC1.4 (PC15-OSC32_OUT)
ENC_CLICK: SW1.E (2), UC1.2 (PC13-TAMPER-RTC)
FINE_TUNE: C31.1, R19.P$2 (2), UC1.13 (PA3/USART2_RX/ADC12_IN3/TIM2_CH4)
FM_CV: IC4.4 (CH3); also elsewhere on the board
GATE: UC1.14 (PA4/SPI1_NSS/USART2_CK/ADC12_IN4); also elsewhere on the board
GND: C3.2, C5.2, C6.2, C7.2, C11.2, C12.2, C31.2, IC4.7 (DGND), IC4.12 (AGND), IC5.8 (GND), JP2.3, JP2.5, JP2.9, JP6.1, JP9.1, JP10.1, JP12.1, JP13.1, JP14.1, Q5.GND, R19.P$1 (1), R33.1, SW1.C, SW1.D (1), UC1.8 (VSS_A), UC1.20 (PB2/BOOT1), UC1.23 (VSS_1), UC1.35 (VSS_2), UC1.46 (PB9/TIM4_CH4), UC1.47 (VSS_3); also elsewhere on the board
JTCK: JP2.4, UC1.37 (PA14/JTCK/SWCLK)
JTDI: JP2.8, UC1.38 (PA15/JTDI)
JTDO: JP2.6, UC1.39 (PB3/JTDO)
JTMS: JP2.2, UC1.34 (PA13/JTMS/SWDIO)
unnamed: Q5.X1, UC1.5 (PD0-OSC_IN)
unnamed: Q5.X2, UC1.6 (PD1-OSC_OUT)
PARAM1_CV: IC4.1 (CH0); also elsewhere on the board
PARAM2_CV: IC4.2 (CH1); also elsewhere on the board
PITCH_CV: IC4.3 (CH2); also elsewhere on the board
RESET: JP2.10, R22.1, UC1.7 (NRST)
RX: UC1.31 (PA10/USART1_RX/TIM1_CH3)
TX: UC1.30 (PA9/USART1_TX/TIM1_CH2)

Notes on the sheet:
cc-by-sa
Codex-Modulex
info@codex-modulex.com
mini JTAG
Digital section
grounded on v4.0 or above
Original design by: Olivier Gillet of Mutable Instruments
